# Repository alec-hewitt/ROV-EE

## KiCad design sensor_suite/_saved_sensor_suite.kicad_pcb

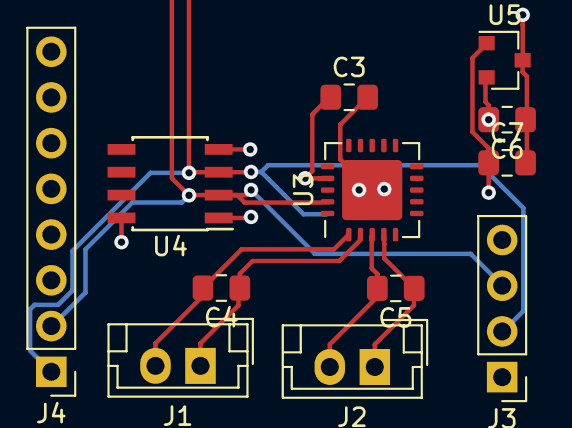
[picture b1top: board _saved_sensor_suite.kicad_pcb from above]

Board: 4 copper layers, 12 parts (0 on the bottom side), 10 nets.

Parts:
C3, C6, C7: 0.1uF; C_0805_2012Metric_Pad1.15x1.40mm_HandSolder
C4, C5: 100pF; C_0805_2012Metric_Pad1.15x1.40mm_HandSolder
J1, J2: Conn_01x02; JST_EH_B02B-EH-A_1x02_P2.50mm_Vertical
J3: Bar02; PinHeader_1x04_P2.54mm_Vertical
J4: LSM303; PinHeader_1x08_P2.54mm_Vertical
U3: MAX6581; QFN-20-1EP_5x5mm_P0.65mm_EP3.35x3.35mm
U4: ADuM1250; SOIC-8_3.9x4.9mm_P1.27mm
U5: LM3480-3.3; SOT-23

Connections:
+3V3: C3.1, C7.1, J3.1, J4.7, J4.8, U3.17, U4.1, U5.1
+12P: C6.2, U5.2
/SCL1: J3.2, J4.1, U3.20, U4.3
/SDA1: J3.3, J4.2, U3.19, U4.2
/temp1n: C4.2, J1.2, U3.1
/temp1p: C4.1, J1.1, U3.2
/temp2n: C5.2, J2.2, U3.3
/temp2p: C5.1, J2.1, U3.4
GND: C6.1, C7.2, U5.3
GNDS: C3.2, J3.4, J4.6, U3.21, U4.4

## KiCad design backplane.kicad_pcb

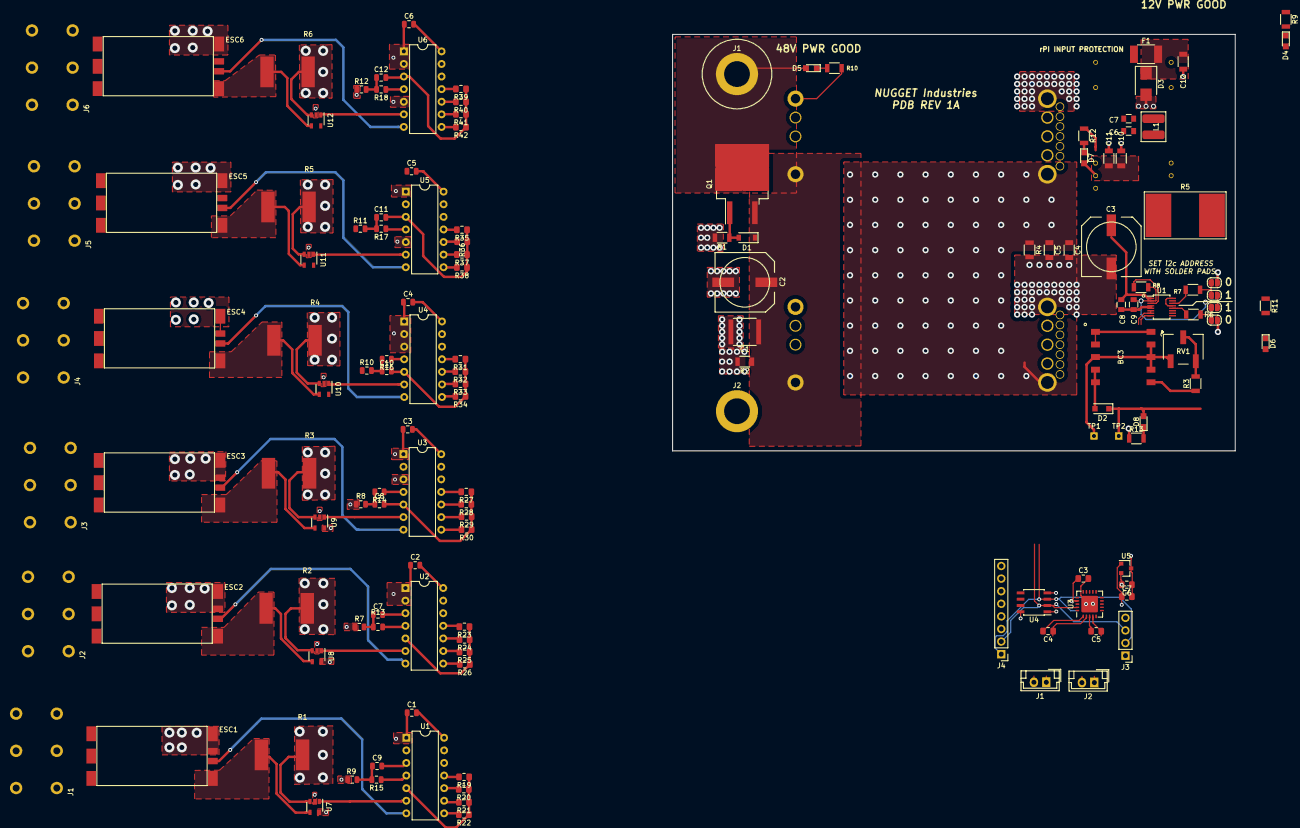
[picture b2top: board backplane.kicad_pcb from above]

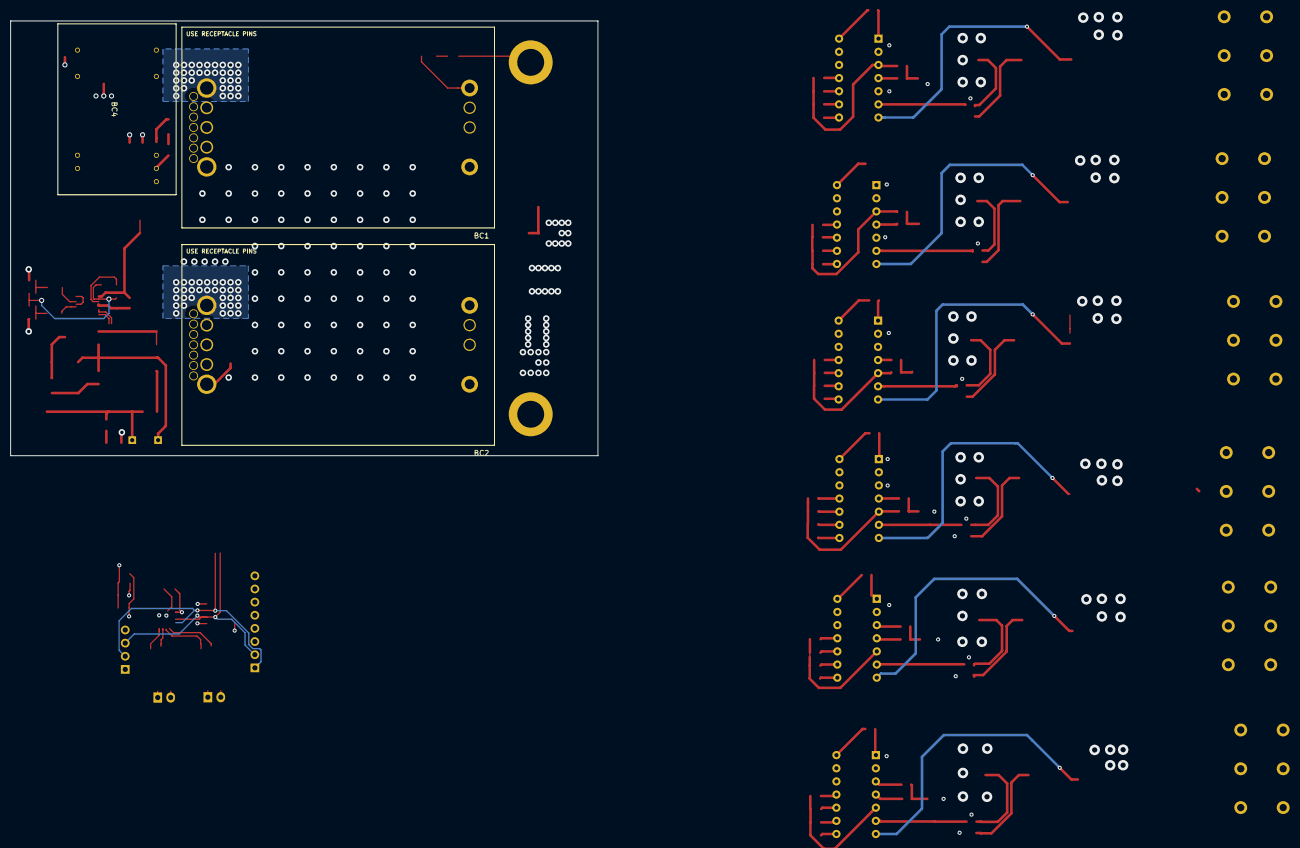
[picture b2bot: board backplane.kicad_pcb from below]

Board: 4 copper layers, 113.5 x 84.0 mm, 140 parts (3 on the bottom side), 107 nets.

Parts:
BC1, BC2: DS_Q48SC12050NRII; DS_Q48SC12050
BC3: R-78AA-1.0; R78AA-1.0
BC4: JTF1524S05
C1, C2#2, C3#2, C4#2, C5#2, C6#2: .1uF; C_0805_2012Metric
C1#2: 10uF; C_2220
C2: 100uF; PCR1J101MCL1GS
C3: 330uF; PCR1J101MCL1GS
C3#3, C6#3, C7#3: 0.1uF; C_0805_2012Metric_Pad1.15x1.40mm_HandSolder
C4, C10: 10uF; C_1206
C4#3, C5#3: 100pF; C_0805_2012Metric_Pad1.15x1.40mm_HandSolder
C5, C11: 1uF; C_1206
C6, C7: 2.2uF; C_0805
C7#2, C8#2, C9, C10#2, C11#2, C12#2: 10nF; C_0805_2012Metric
C8, C9#2: .1uF; C_0805
C12: 47uF; C_1206
D1: 12V; D_SOD-123
D2: D_Small_ALT; D_SOD-123F
D3: SMBJ5.0A-13-F; D_SMB
D4, D5, D6, D7, D8: LED; LED_0805
ESC1, ESC2, ESC3, ESC4, ESC5, ESC6: ESC
F1: MF-MSMF250/16X-2; R_1812
J1, J2#2, J3, J4, J5, J6: Conn_01x03_Female; Wago Terminal Blocks
J1#2, J2: Conn_01x01; 7466004
J1#3, J2#3: Conn_01x02; JST_EH_B02B-EH-A_1x02_P2.50mm_Vertical
J3#2: Bar02; PinHeader_1x04_P2.54mm_Vertical
J4#2: LSM303; PinHeader_1x08_P2.54mm_Vertical
JP1, JP2, JP3, JP4: SolderJumper_2_Open; SolderJumper-2_P1.3mm_Open_RoundedPad1.0x1.5mm
L1: 12uH; SDE0403A-120M
Q1: Q_PMOS_GDS; TO-263-2
R1, R2#2, R3#2, R4#2, R5#2, R6#2: WSLP59311L000FEB; Shunt Resistor
R1#2: 100K; R_1206
R2: 12K; R_1206
R3: 470K; R_1206
R4: 3.3K; R_1206
R5: WSLP59311L000FEB
R6, R7: 22K; R_1206
R7#2, R8#2, R9, R10#2, R11#2, R12#2: 10k; R_0805_2012Metric
R8: 4.7K; R_1206
R9#2, R11, R12, R13: 600; R_1206
R10: 2.4K; R_1206
R13#2, R14, R15, R16, R17, R18: 100; R_0805_2012Metric
R19, R20, R21, R22, R24, R25, R26, R28, R29, R30, R36, R37, R38, R40, R41, R42: 1k; R_0805_2012Metric_Pad1.15x1.40mm_HandSolder
R23, R27, R31, R32, R33, R34, R35, R39: R_Small; R_0805_2012Metric_Pad1.15x1.40mm_HandSolder
RV1: 200k; 3269W-1-204GLF
TP1, TP2: TestPoint; Measurement_Point_Square-TH_Small
U1, U2, U3, U4, U5, U6: PIC16F15323; DIP-14_W7.62mm
U1#2: LTC2946CMS#PBF; MSOP-16_3x4mm_Pitch0.5mm
U3#2: MAX6581; QFN-20-1EP_5x5mm_P0.65mm_EP3.35x3.35mm
U4#2: ADuM1250; SOIC-8_3.9x4.9mm_P1.27mm
U5#2: LM3480-3.3; SOT-23
U7, U8, U9, U10, U11, U12: TSC888; SOT-23-5

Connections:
5VPI: C12.2, D3.1, F1.2
+3V3: C3#3.1, C7#3.1, J3#2.1, J4#2.7, J4#2.8, U3#2.17, U4#2.1, U5#2.1
+5V: BC4.14, C10.2, C11.2, D7.2, F1.1
+5VP: C1.1, C2#2.1, C3#2.1, C4#2.1, C5#2.1, C6#2.1, D2.1, D8.2, R7#2.1, R8#2.1, R9.1, R10#2.1, R11#2.1, R12#2.1, TP2.1, U1.1, U2.1, U2.2, U3.1, U3.3, U4.1, U4.2, U4.3, U4#2.8, U5.1, U5.5, U6.1, U6.2, U6.5, U7.5, U8.5, U9.5, U10.5, U11.5, U12.5
+12P: BC3.1, BC3.2, BC3.10, C6.2, C6#3.2, L1.1, R1.1, R2#2.1, R3#2.1, R4#2.1, R5.2, R5#2.1, R6#2.1, U1#2.15, U5#2.2, U7.3, U8.3, U9.3, U10.3, U11.3, U12.3
+48V: D5.2, J1#2.1, Q1.2
/ADR0: R6.1, U1#2.12
/ADR1: R7.1, U1#2.14
/CS1: U1.6, U7.1
/CS2: U2.6, U8.1
/CS3: U3.6, U9.1
/CS4: U4.6, U10.1
/CS5: U5.6, U11.1
/CS6: U6.6, U12.1
/GP_OUTPUT: R8.2, U1#2.3
/INTVCC: C9#2.2, JP1.1, JP3.1, R8.1, U1#2.2
/PWM1: ESC1.2, U1.7
/PWM2: ESC2.2, U2.7
/PWM3: ESC3.2, U3.7
/PWM4: ESC4.2, U4.7
/PWM5: ESC5.2, U5.7
/PWM6: ESC6.2, U6.7
/SCL1: J3#2.2, J4#2.1, U3#2.20, U4#2.3
/SDA1: J3#2.3, J4#2.2, U3#2.19, U4#2.2
/SDAISO: U1#2.6, U1#2.7
/VIN+: BC1.1, BC2.1, C1#2.1, C2.1, D1.1, Q1.3, R2.1
/VOUT: BC1.9, BC2.9, C3.1, C4.1, C5.1, C8.2, D4.2, D6.2, R4.1, R5.1, U1#2.1, U1#2.13, U1#2.16
/temp1n: C4#3.2, J1#3.2, U3#2.1
/temp1p: C4#3.1, J1#3.1, U3#2.2
/temp2n: C5#3.2, J2#3.2, U3#2.3
/temp2p: C5#3.1, J2#3.1, U3#2.4
Earth: BC1.2, BC1.4, BC2.2, BC2.4, C1#2.2, C2.2, J2.1, R1#2.2, R2.2, R10.1
GND: C6#3.1, C7#3.2, U5#2.3
GNDPWR: BC1.5, BC2.5, BC3.3, BC3.7, BC3.8, BC3.9, BC4.2, BC4.3, C1.2, C2#2.2, C3.2, C3#2.2, C4.2, C4#2.2, C5.2, C5#2.2, C6.1, C6#2.2, C7.1, C7#2.2, C8.1, C8#2.2, C9.2, C9#2.1, C10#2.2, C11#2.2, C12#2.2, ESC1.3, ESC1.4, ESC2.3, ESC2.4, ESC3.3, ESC3.4, ESC4.3, ESC4.4, ESC5.3, ESC5.4, ESC6.3, ESC6.4, JP2.1, JP4.1, R4.2, R9#2.1, R11.1, R13.1, R19.1, R20.1, R21.1, R22.1, R23.1, R24.1, R25.1, R26.1, R27.1, R28.1, R29.1, R30.1, R31.1, R32.1, R33.1, R34.1, R35.1, R36.1, R37.1, R38.1, R39.1, R40.1, R41.1, R42.1, RV1.1, TP1.1, U1.2, U1.3, U1.5, U1.14, U1#2.4, U1#2.5, U1#2.9, U1#2.11, U2.3, U2.5, U2.14, U3.2, U3.5, U3.14, U4.5, U4.14, U4#2.5, U5.2, U5.3, U5.14, U6.3, U6.14, U7.2, U8.2, U9.2, U10.2, U11.2, U12.2
GNDS: BC4.16, C3#3.2, C10.1, C11.1, C12.1, D3.2, J3#2.4, J4#2.6, R12.1, U3#2.21, U4#2.4
unnamed: BC3.4, BC3.5, D2.2
unnamed: BC3.6, R3.1
unnamed: BC4.22, BC4.23, C7.2, L1.2
unnamed: C7#2.1, R7#2.2, R13#2.2
unnamed: C8#2.1, R8#2.2, R14.2
unnamed: C9.1, R9.2, R15.2
unnamed: C10#2.1, R10#2.2, R16.2
unnamed: C11#2.1, R11#2.2, R17.2
unnamed: C12#2.1, R12#2.2, R18.2
unnamed: D1.2, Q1.1, R1#2.1
unnamed: D4.1, R9#2.2
unnamed: D5.1, R10.2
unnamed: D6.1, R11.2
unnamed: D7.1, R12.2
unnamed: D8.1, R13.2
unnamed: ESC1.1, R1.2, U7.4
unnamed: ESC1.5, J1.1
unnamed: ESC1.6, J1.2
unnamed: ESC1.7, J1.3
unnamed: ESC2.1, R2#2.2, U8.4
unnamed: ESC2.5, J2#2.1
unnamed: ESC2.6, J2#2.2
unnamed: ESC2.7, J2#2.3
unnamed: ESC3.1, R3#2.2, U9.4
unnamed: ESC3.5, J3.1
unnamed: ESC3.6, J3.2
unnamed: ESC3.7, J3.3
unnamed: ESC4.1, R4#2.2, U10.4
unnamed: ESC4.5, J4.1
unnamed: ESC4.6, J4.2
unnamed: ESC4.7, J4.3
unnamed: ESC5.1, R5#2.2, U11.4
unnamed: ESC5.5, J5.1
unnamed: ESC5.6, J5.2
unnamed: ESC5.7, J5.3
unnamed: ESC6.1, R6#2.2, U12.4
unnamed: ESC6.5, J6.1
unnamed: ESC6.6, J6.2
unnamed: ESC6.7, J6.3
unnamed: JP1.2, JP2.2, R6.2
unnamed: JP3.2, JP4.2, R7.2
unnamed: R3.2, RV1.2, RV1.3
unnamed: R13#2.1, U2.4
unnamed: R14.1, U3.4
unnamed: R15.1, U1.4
unnamed: R16.1, U4.4
unnamed: R17.1, U5.4
unnamed: R18.1, U6.4
unnamed: R19.2, U1.11
unnamed: R20.2, U1.10
unnamed: R21.2, U1.9
unnamed: R22.2, U1.8
unnamed: R23.2, U2.11
unnamed: R24.2, U2.10
unnamed: R25.2, U2.9
unnamed: R26.2, U2.8
unnamed: R27.2, U3.11
unnamed: R28.2, U3.10
unnamed: R29.2, U3.9
unnamed: R30.2, U3.8
unnamed: R31.2, U4.11
unnamed: R32.2, U4.10
unnamed: R33.2, U4.9
unnamed: R34.2, U4.8
unnamed: R35.2, U5.11
unnamed: R36.2, U5.10
unnamed: R37.2, U5.9
unnamed: R38.2, U5.8
unnamed: R39.2, U6.11
unnamed: R40.2, U6.10
unnamed: R41.2, U6.9
unnamed: R42.2, U6.8

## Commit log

2018-12-03 Base project
2018-12-16 heigharcal names should be correct accross all boards. layouts are together in the backplane.pcb file, except for the pi and PCA. ESC breakout layout tightened up.
